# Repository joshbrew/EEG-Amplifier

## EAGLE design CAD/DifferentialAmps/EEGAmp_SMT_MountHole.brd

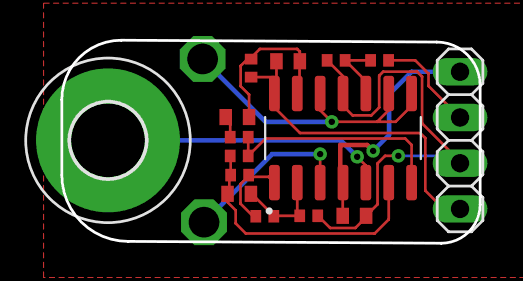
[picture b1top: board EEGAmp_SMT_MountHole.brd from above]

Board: 2 copper layers, 23.2 x 11.3 mm, 17 parts (0 on the bottom side), 14 nets.

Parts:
AIN-: PTR1PAD1-17; P1-17
C1, C2, C3: C0402
C4: 2.2nF; C0402
H1: MOUNT-PAD-ROUND4.1; 4,1-PAD
JP2: 1X04
R1, R2, R3, R4, R5, R6, R7, R8: R0402
REFOUT: PTR1PAD1-17; P1-17
U1: TL084QD; SOIC127P600X175-14N

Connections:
1IN-: C4.2, R2.2, R3.1, U1.2
1OUT: R1.1, R3.2, U1.1
2IN-: C4.1, R1.2, R4.1, U1.6
3IN+: R5.1, R6.2, U1.10
4IN-: C1.2, C2.1, R8.1, U1.13
AIN+: H1.B4,1, U1.5
AIN-: AIN-.TP, U1.3
AOUT: C2.2, JP2.4, R8.2, U1.14
GND: C3.1, JP2.3, R2.1, R6.1, U1.11
unnamed: C1.1, R7.2
REFOUT: REFOUT.TP, U1.8, U1.9, U1.12
VDD: C3.2, JP2.1, U1.4
VOD: R4.2, R7.1, U1.7
VREF: JP2.2, R5.2

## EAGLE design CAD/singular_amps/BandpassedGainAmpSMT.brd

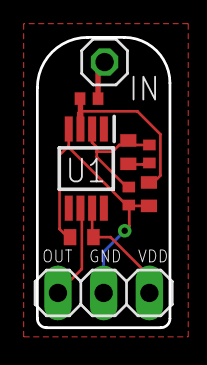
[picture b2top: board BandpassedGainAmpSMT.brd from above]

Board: 2 copper layers, 7.4 x 16.1 mm, 9 parts (0 on the bottom side), 7 nets.

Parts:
C1, C2, C3: C0402
IN: 1X01
JP1: 1X03
R1, R2: R0402
R3: 1K; R0402
U1: OPA202IDGKR; SOP65P490X110-8N

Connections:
+IN: C1.2, R3.2, U1.3
-IN: C2.1, R1.2, R2.1, U1.2
GND: C1.1, C3.1, JP1.2, R1.1, U1.4
IN: IN.1, R3.1
unnamed: C2.2, R2.2
OUT: JP1.3, U1.6
VDD: C3.2, JP1.1, U1.7

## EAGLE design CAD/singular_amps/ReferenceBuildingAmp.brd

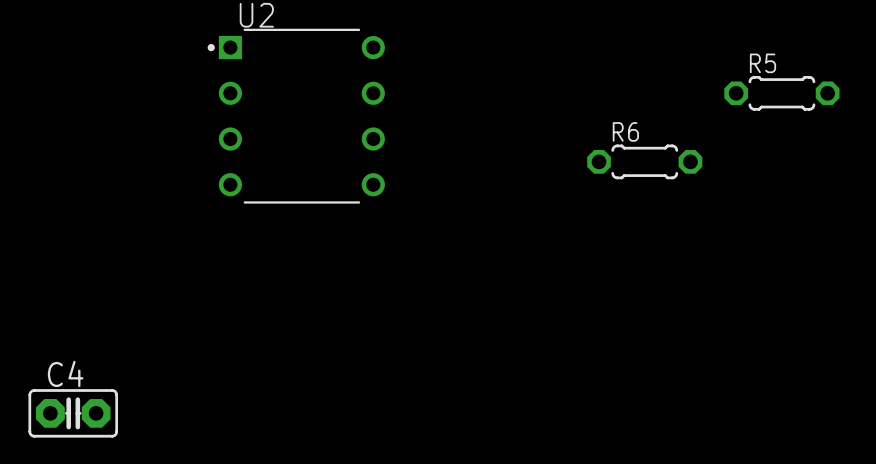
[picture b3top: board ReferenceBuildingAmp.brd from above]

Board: 2 copper layers, 4 parts (0 on the bottom side), 4 nets, no tracks yet.

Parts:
C4: C2.5-2
R5, R6: 0204/5
U2: TL081CP; DIP794W45P254L959H508Q8

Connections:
3IN+: R5.1, R6.2, U2.3
GND: C4.1, R6.1
VDD: C4.2, R5.2
VREF: U2.2, U2.6
